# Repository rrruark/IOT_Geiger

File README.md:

http://robruark.com/other/Radiation/Geiger_Counter/v2/geiger_v23.html

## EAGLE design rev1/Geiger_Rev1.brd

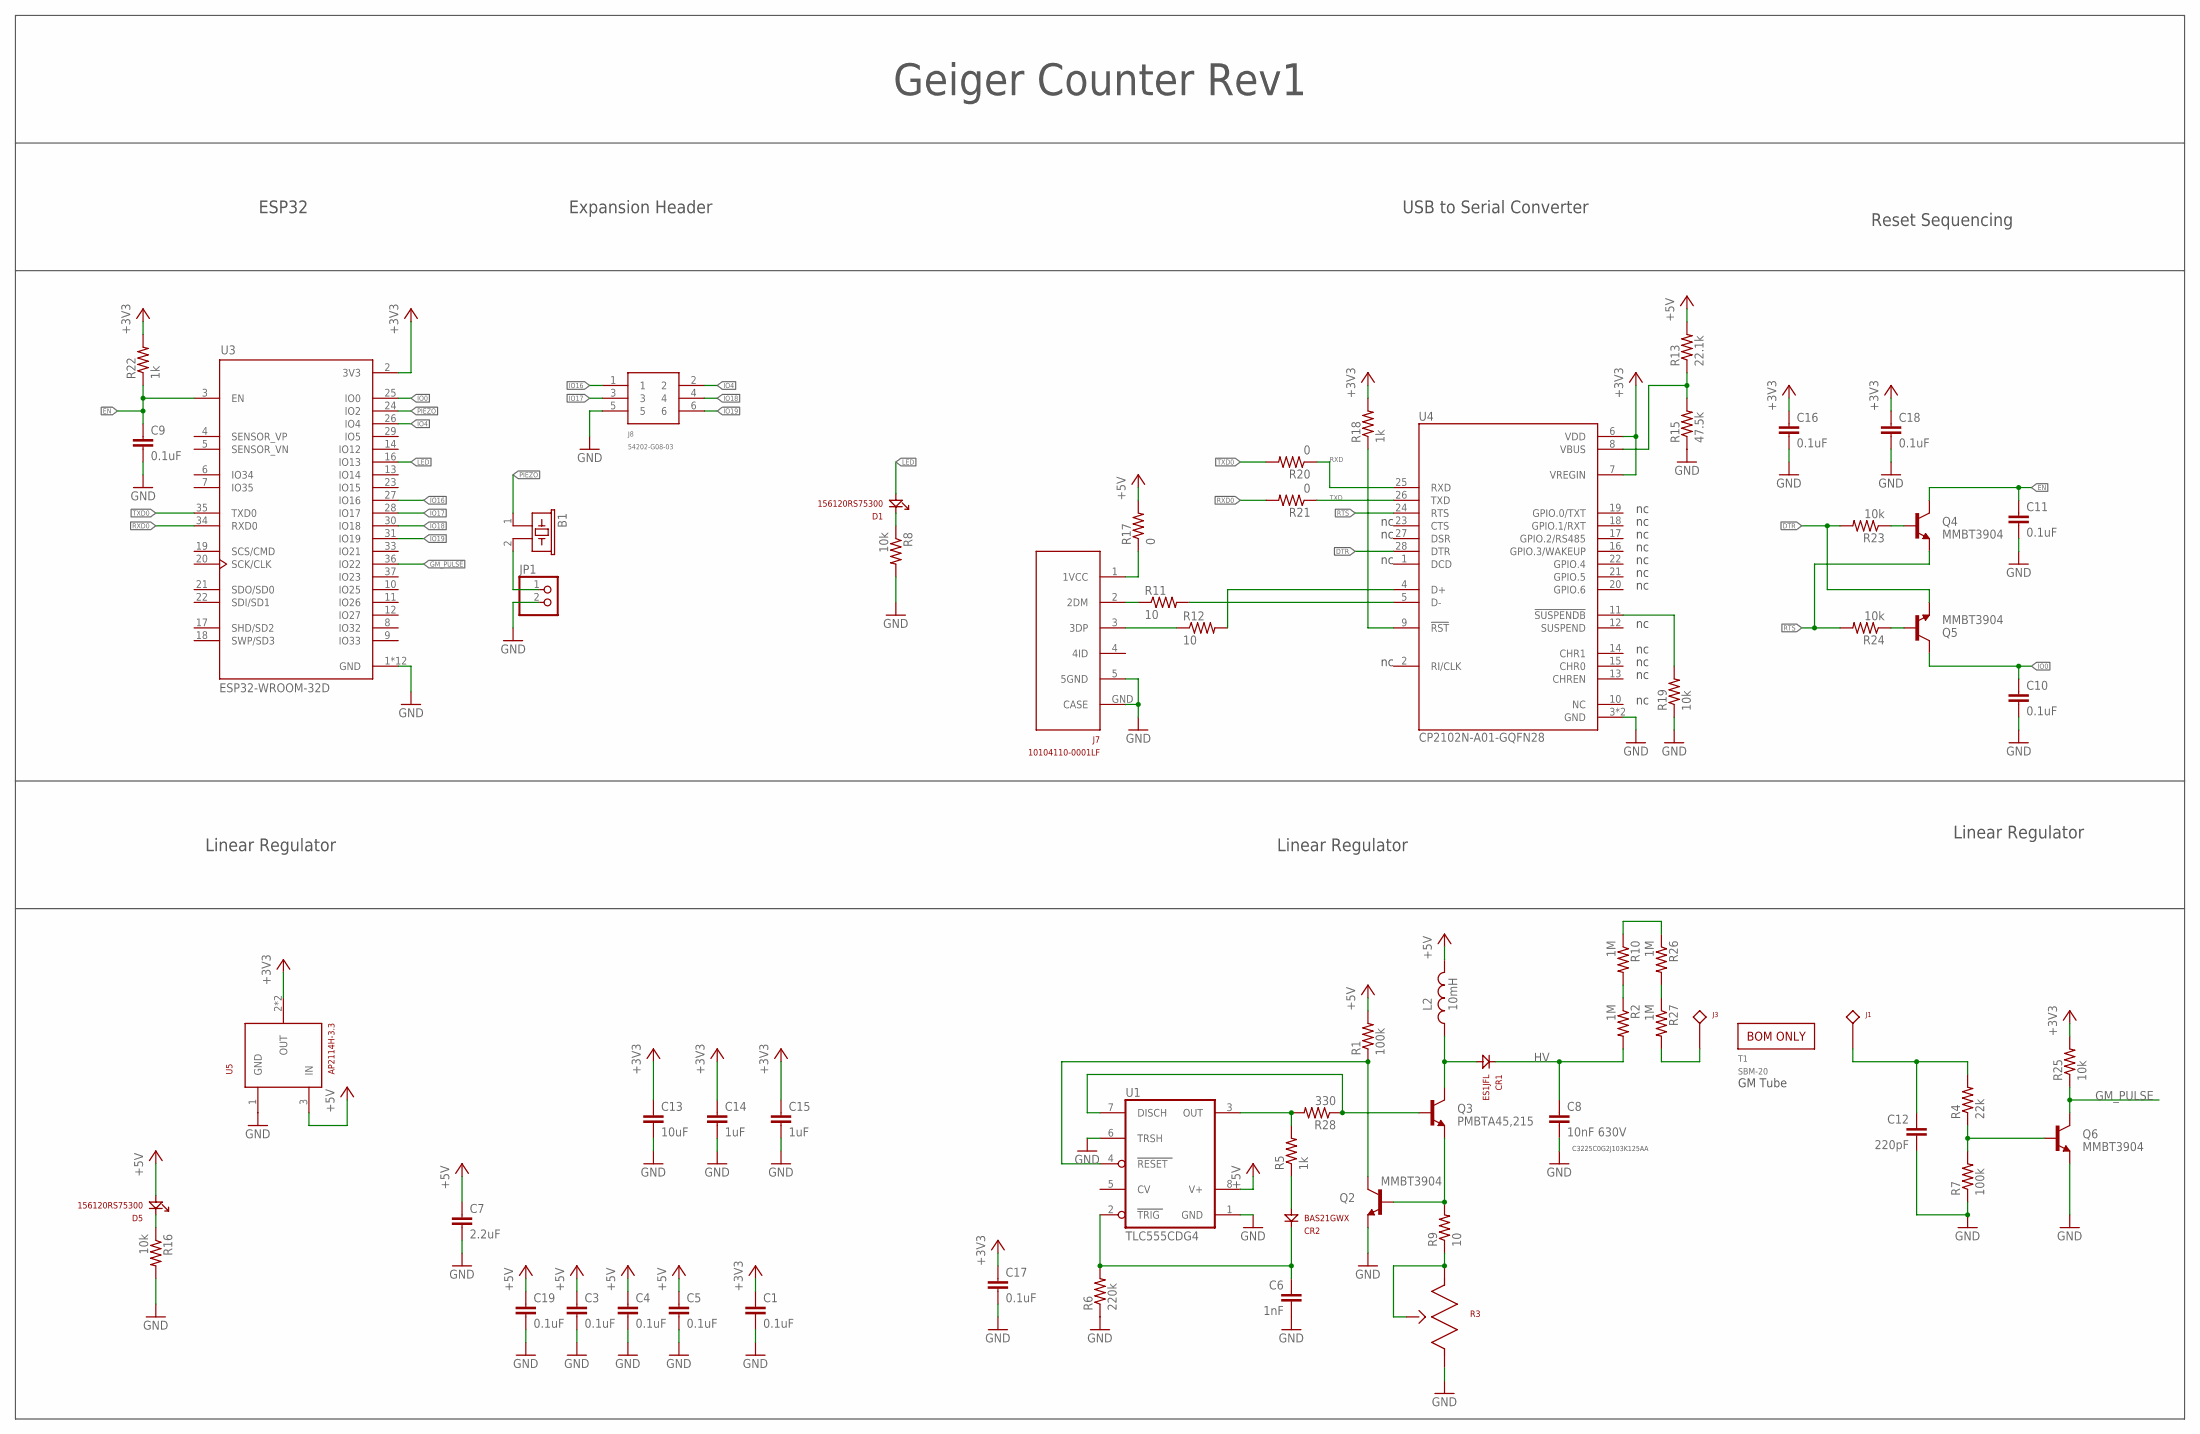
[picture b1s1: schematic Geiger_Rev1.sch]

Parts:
B1: PIEZO17MM; PS1740P02E
C1, C3, C4, C5, C9, C10, C11, C16, C17, C18, C19: 0.1uF; 0603
C6: 1nF; 0603
C7: 2.2uF; 1210
C8: 10nF 630V; 1210
C12: 220pF; 0603
C13: 10uF; 0805
C14, C15: 1uF; 0805
CR1: ES1JFL; SOD123(AK)
CR2: BAS21GWX; SOD123
D1, D5: 156120RS75300; 1206_REV
J1, J3: 01010002Z
J7: 10104110-0001LF; MICRO_USB
J8: 54202-G08-03; 6-SMT-HEADER
JP1: PINHD-1X2; 1X02
L2: 10mH; SDR1005
Q2, Q4, Q5, Q6: MMBT3904; SOT23-3
Q3: PMBTA45,215; SOT23-3
R1, R7: 100k; 0603
R2, R10, R26, R27: 1M; 0603
R3: 10; 3361P
R4: 22k; 0603
R5, R18, R22: 1k; 0603
R6: 220k; 0603
R8, R16, R19, R23, R24, R25: 10k; 0603
R9: 10; 1206
R11, R12: 10; 0603
R13: 22.1k; 0603
R15: 47.5k; 0603
R17, R20, R21: 0; 0603
R28: 330; 0603
T1: SBM-20
U1: TLC555CDG4; SOIC8
U3: ESP32-WROOM-32D; MODULE_ESP32-WROOM-32D
U4: CP2102N-A01-GQFN28; QFN50P500X500X80-29N
U5: AP2114H-3.3; SOT223

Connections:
+3V3: C1.1, C13.1, C14.1, C15.1, C16.1, C17.1, C18.1, R18.2, R22.2, R25.2, U3.2 (3V3), U4.6 (VDD), U4.7 (VREGIN), U5.2 (OUT), U5.T (OUT)
+5V: C3.1, C4.1, C5.1, C7.1, C19.1, D5.A, L2.P$2, R1.2, R13.2, R17.2, U1.8 (V+), U5.3 (IN)
DTR: Q5.2 (E), R23.2, U4.28 (DTR)
EN: C9.1, C11.1, Q4.3 (C), R22.1, U3.3 (EN)
GM_PULSE: Q6.3 (C), R25.1, U3.36 (IO22)
GND: C1.2, C3.2, C4.2, C5.2, C6.2, C7.2, C8.2, C9.2, C10.2, C11.2, C12.2, C13.2, C14.2, C15.2, C16.2, C17.2, C18.2, C19.2, J7.5 (5GND), J7.GND (CASE), J8.5, JP1.2, Q2.2 (E), Q6.2 (E), R3.3, R6.1, R7.1, R8.2, R15.1, R16.2, R19.1, U1.1 (GND), U1.6 (TRSH), U3.1 (GND), U3.15 (GND), U3.38 (GND), U3.39_1 (GND), U3.39_2 (GND), U3.39_3 (GND), U3.39_4 (GND), U3.39_5 (GND), U3.39_6 (GND), U3.39_7 (GND), U3.39_8 (GND), U3.39_9 (GND), U4.3 (GND), U4.29 (GND), U5.1 (GND)
HV: C8.1, CR1.K, R2.2
IO0: C10.1, Q5.3 (C), U3.25 (IO0)
IO4: J8.2, U3.26 (IO4)
IO16: J8.1, U3.27 (IO16)
IO17: J8.3, U3.28 (IO17)
IO18: J8.4, U3.30 (IO18)
IO19: J8.6, U3.31 (IO19)
LED: D1.A, U3.16 (IO13)
unnamed: CR2.2 (A), R5.1
unnamed: J7.2 (2DM), R11.1
unnamed: Q2.3 (C), R1.1, U1.4 (RESET)
unnamed: J7.3 (3DP), R12.1
unnamed: R11.2, U4.5 (D-)
unnamed: R12.2, U4.4 (D+)
unnamed: R13.1, R15.2, U4.8 (VBUS)
unnamed: Q3.1 (B), R28.1, U1.7 (DISCH)
unnamed: C6.1, CR2.1 (K), R6.2, U1.2 (TRIG)
unnamed: R5.2, R28.2, U1.3 (OUT)
unnamed: Q2.1 (B), Q3.2 (E), R9.2
unnamed: B1.2, JP1.1
unnamed: J7.1 (1VCC), R17.1
unnamed: Q6.1 (B), R4.1, R7.2
unnamed: J3.P$1, R27.2
unnamed: R2.1, R10.2
unnamed: R10.1, R26.1
unnamed: R18.1, U4.9 (!RST)
unnamed: D5.K, R16.1
unnamed: R19.2, U4.11 (!SUSPENDB)
unnamed: R26.2, R27.1
unnamed: Q4.1 (B), R23.1
unnamed: R3.1, R3.2, R9.1
unnamed: Q5.1 (B), R24.1
unnamed: D1.K, R8.1
unnamed: C12.1, J1.P$1, R4.2
PIEZO: B1.1, U3.24 (IO2)
RTS: Q4.2 (E), R24.2, U4.24 (RTS)
RXD: R20.1, U4.25 (RXD)
RXD0: R21.2, U3.34 (RXD0)
SW: CR1.A, L2.P$1, Q3.3 (C)
TXD: R21.1, U4.26 (TXD)
TXD0: R20.2, U3.35 (TXD0)

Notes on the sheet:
Geiger Counter Rev1
Linear Regulator
GM Tube
C3225C0G2J103K125AA
ESP32
Expansion Header
USB to Serial Converter
Reset Sequencing

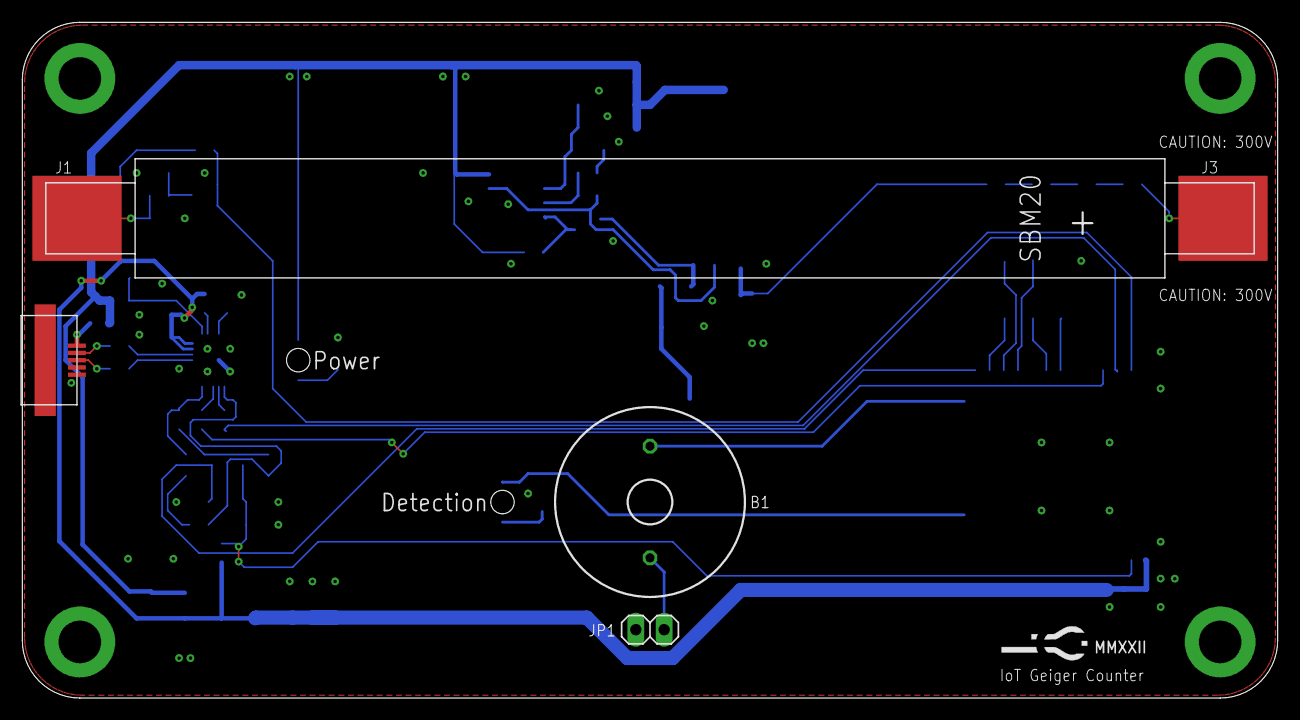
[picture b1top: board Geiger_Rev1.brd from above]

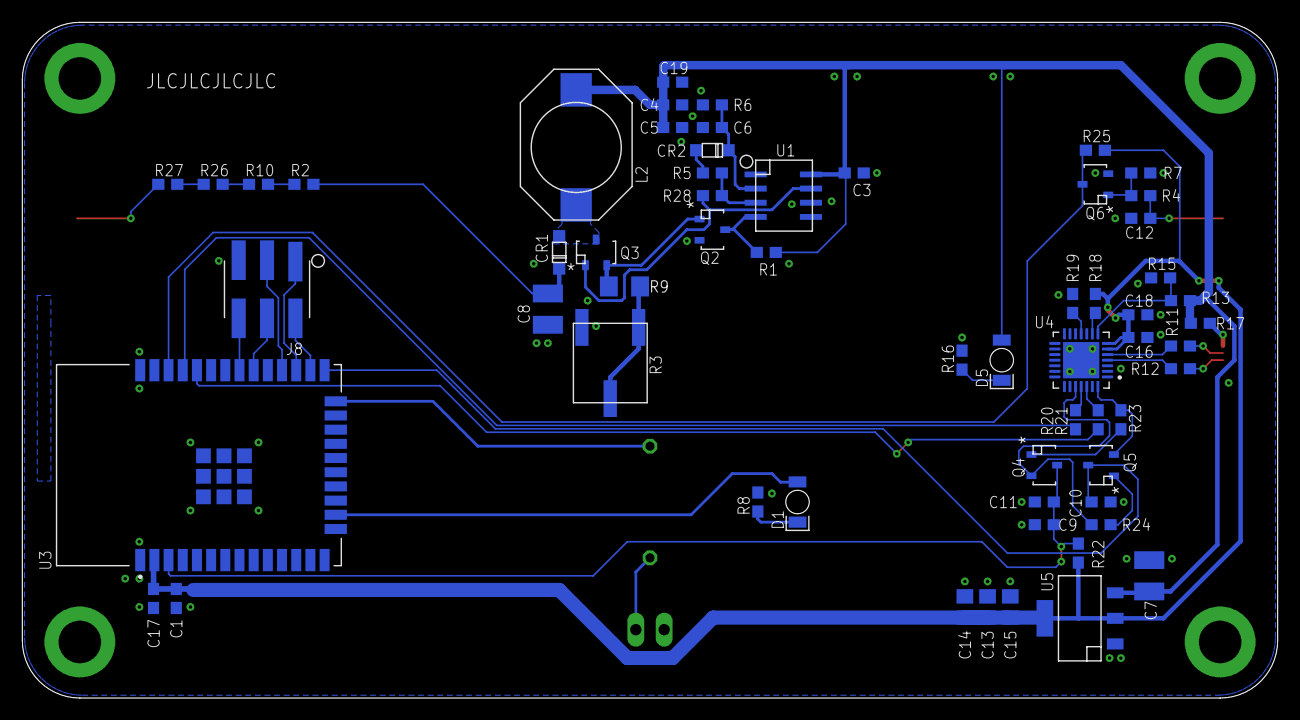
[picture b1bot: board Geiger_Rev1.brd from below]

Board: 2 copper layers, 112.4 x 60.5 mm, 66 parts (60 on the bottom side), 47 nets.

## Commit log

2024-05-05 release
2024-06-16 Directory cleanup
2024-06-16 Adding Arduino code
